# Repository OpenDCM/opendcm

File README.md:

# opendcm
Open DC multimeter.

This repository contain sources for building DC Multimeter.
Project information can be found at :
http://opendcm.blogspot.bg/

The project is still under developing.

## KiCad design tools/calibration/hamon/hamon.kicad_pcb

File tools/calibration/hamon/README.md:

Kicad project for Hamon 1:10 Resistive Divider.

Resistor values can be calculated with the Hamon_calc.ods file.

The first prototype will use :
- S102K 5K resistors for R1-3 
- RCK02 for R4 - 1K8 and R5 - 22K
- Accutrim 1280G 1K trimmer
- 2 SA404 banana plugs for direct connection to the 10V LTZ1000 Voltage Reference Standard
- 2 Pomona 3750 binding posts for cable connection to the DMM
- DPST switch M2021SS1W01 with low contact resistance

Files:<br>
hamon.kicad\_pcb - hamon divider PCB with 2 banana plugs (SA404) and 2 binding posts.<br>
hamon\_bp.kicad\_pcb - hamon divider PCB with 4 binding posts.<br>
Hamon\_calc.ods - spreadsheet for resistor calculation.<br>

Preliminary test:
Setup with Advantest R6581T:

Setup with HP 34401A:

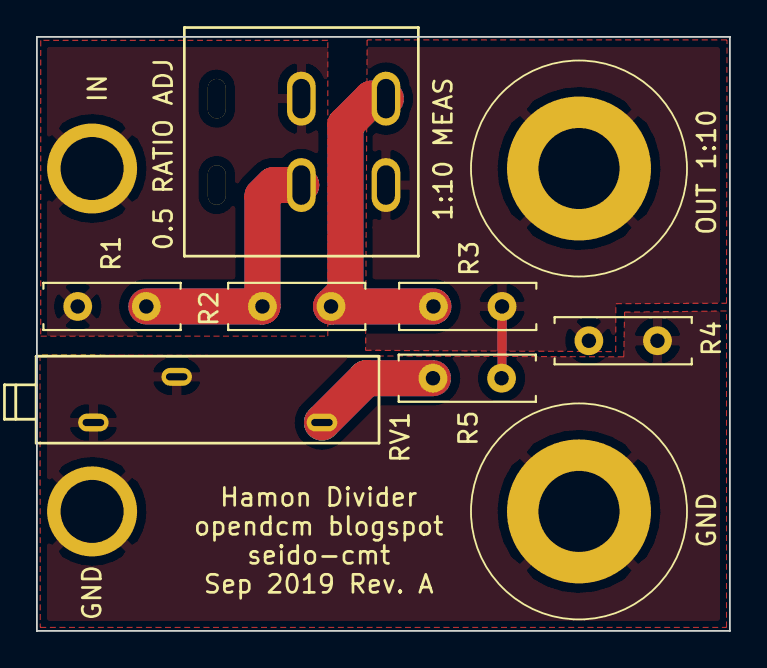
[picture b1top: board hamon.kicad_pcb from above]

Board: 2 copper layers, 38.5 x 33.0 mm, 11 parts (0 on the bottom side), 6 nets.

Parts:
H1: Input; SA404
H2: GND; SA404
H3: Output; Binding_Post_4mm
H4: GND; Binding_Post_4mm
R1, R2, R3, R4, R5: R; Vishay_L7.62mm_D2.67mm_P3.81mm_Horizontal
RV1: R_POT; Accutrim_1280G_1285G
SW1: SW_DPST; M2021SS1W01

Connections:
GND: H2.1, H4.1, R4.2, RV1.2, RV1.3
IN: H1.1, R1.1, SW1.2
unnamed: R1.2, R2.1, SW1.5
unnamed: R2.2, R3.1, SW1.3
unnamed: R5.2, RV1.1
OUT: H3.1, R3.2, R4.1, R5.1, SW1.6

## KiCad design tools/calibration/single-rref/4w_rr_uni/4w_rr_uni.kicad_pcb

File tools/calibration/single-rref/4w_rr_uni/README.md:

This is universal PCB for single resistor reference.
Includes :
- 4 wire connection to the resistor
- Connections with 4 mm banana binding posts and with 4mm banana plugs
- 4 wire connection with pt100 sensor
- I2C EEPROM for storing calibration data

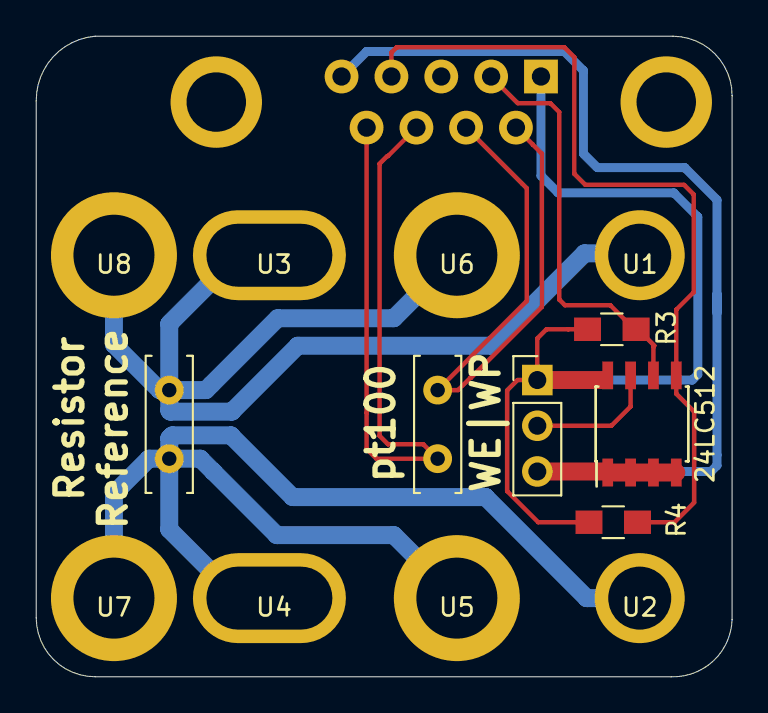
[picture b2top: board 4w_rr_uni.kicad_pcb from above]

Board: 2 copper layers, 38.7 x 35.6 mm, 15 parts (0 on the bottom side), 9 nets.

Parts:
J1: DB9; DB9_horizontal
J2: Conn_01x03; Pin_Header_Straight_1x03_Pitch2.54mm
R1, R2: R; Vishay_L7.62mm_D2.67mm_P3.81mm_Horizontal
R3, R4: R; R_0805_HandSoldering
U1, U2: SA404; VIA
U3, U4: SA404; VIA_oval
U5, U6, U7, U8: Banana; Binding_Post_4mm
U9: 24LC512; SOIC-8_3.9x4.9mm_Pitch1.27mm

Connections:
GND: J1.5, J2.3, U9.1, U9.2, U9.3, U9.4
unnamed: J1.2, R3.2, U9.6
unnamed: J1.4, R4.2, U9.5
unnamed: J1.6, J1.7, R2.1
unnamed: J1.8, J1.9, R2.2
unnamed: J2.2, U9.7
unnamed: R1.1, U1.1, U3.1, U6.1, U8.1
unnamed: R1.2, U2.1, U4.1, U5.1, U7.1
VCC: J1.1, J2.1, R3.1, R4.1, U9.8

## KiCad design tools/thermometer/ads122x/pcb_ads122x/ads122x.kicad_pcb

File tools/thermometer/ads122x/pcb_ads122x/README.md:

This is a PCB for ADS1220, ADS122U04 and ADS122C04 ICs from TI.

The PCB can be used as digital thermometer front-end with PT100 platinum resistance sensor.

The Pt100 sensor can be connected in 2,3,4 wire configuration.

The achievable resolution is 0.001C when 1mA current is used with averaging 20 samples per second.

The achievable uncertainty for 1 year (excluding pt100 probe uncertainty), using a reference resistor with stability <25ppm per year and TCR < 2.5/C can be 0.02C (K=2).

The ADS122x IC have two power supplies - analog AVDD and digital DVDD. This version of PCB have common ground between AVDD and DVDD.

The common ground between AVDD and DVDD limits the temperature range to -20 <-> 145C ( min AVDD = 4V, PGA = 16, Rref = 2.5K).

The PCB can fit into BERNIC ABS box type 40x. 

You can find a spreadsheet document (ADS122x_calculator.ods) which helps to calculate optimal power supplies, PGA pass/fail criteria and RC filters

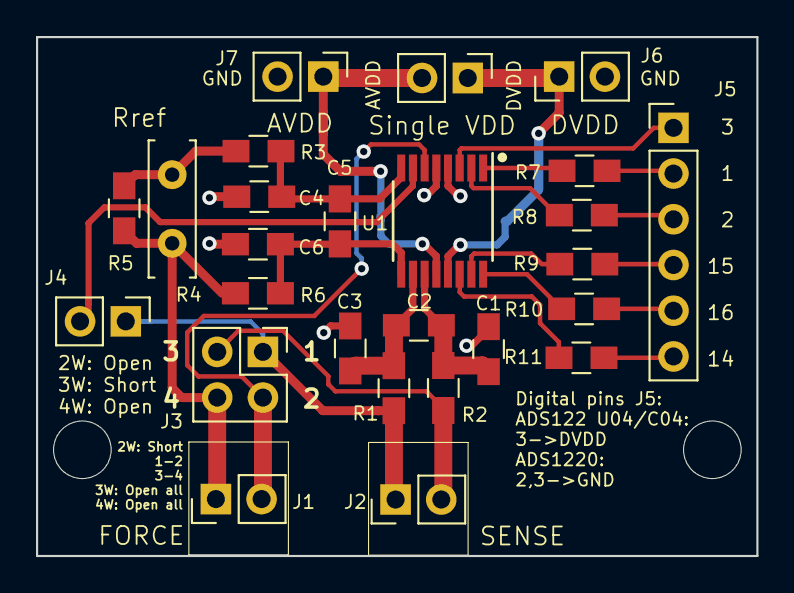
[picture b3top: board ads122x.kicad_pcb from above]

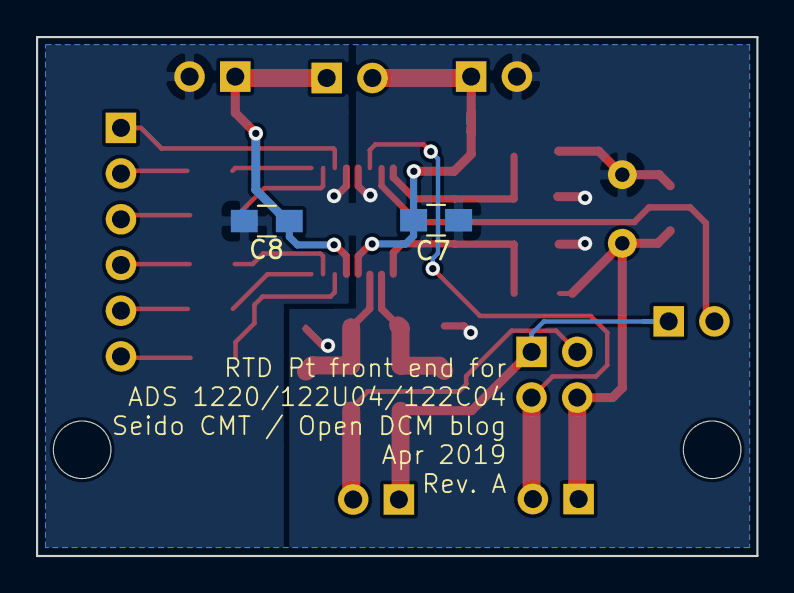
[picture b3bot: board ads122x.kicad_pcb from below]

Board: 2 copper layers, 40.0 x 28.8 mm, 30 parts (2 on the bottom side), 23 nets.

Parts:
C1, C2, C3, C4, C5, C6, C7, C8: C; 0805
H1, H2: MountingHole; MountingHole_3.2mm_M3
J1, J2: Conn_01x02; PCB_Terminal_2_2.54
J3: Conn_02x02_Odd_Even; Pin_Header_Straight_2x02_Pitch2.54mm
J4: Conn_01x02; Pin_Header_Straight_1x02_Pitch2.54mm
J5: Conn_01x06; Pin_Header_Straight_1x06_Pitch2.54mm
J6: Digital Supply; Pin_Header_Straight_1x02_Pitch2.54mm
J7: Analog Supply; Pin_Header_Straight_1x02_Pitch2.54mm
J8: Single Supply; Pin_Header_Straight_1x02_Pitch2.54mm
R1, R2, R3, R5, R6, R7, R8, R9, R10, R11: R; 0805
R4: R; Vishay_L7.62mm_D2.67mm_P3.81mm
U1: ads122x; TSSOP-16_4.4x5mm_Pitch0.65mm

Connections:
AIN0: C1.1, C2.2, R2.2, U1.11
AIN1: C2.1, C3.2, R1.1, U1.10
AIN2: J4.2, U1.7
AIN3: J1.2, J3.2, U1.6
AVDD: C7.2, J7.1, J8.2, U1.12
DVDD: C8.2, J6.1, J8.1, U1.13
GND: C1.2, C3.1, C4.1, C6.1, C7.1, C8.1, J6.2, J7.2, R3.2, R4.2, R5.2, U1.4, U1.5
unnamed: J1.1, J3.4, R4.1, R5.1, R6.2
unnamed: J2.1, J3.1, J4.1, R1.2
unnamed: J2.2, J3.3, R2.1
unnamed: J5.1, U1.3
unnamed: J5.2, R7.1
unnamed: J5.3, R8.1
unnamed: J5.4, R9.1
unnamed: J5.5, R10.1
unnamed: J5.6, R11.1
unnamed: R7.2, U1.1
unnamed: R8.2, U1.2
unnamed: R9.2, U1.15
unnamed: R10.2, U1.16
unnamed: R11.2, U1.14
REFN0: C4.2, C5.2, R3.1, U1.8
REFP0: C5.1, C6.2, R6.1, U1.9

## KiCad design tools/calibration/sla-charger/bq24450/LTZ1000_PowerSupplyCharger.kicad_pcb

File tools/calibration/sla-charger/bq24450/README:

PCB for SLA Battery charger using TI BQ24450 IC.

- Implemention of Fig. 8 and 9a schematics taken from the IC datasheet.
- Darlington transistor.
- Spreadsheet for resisors calculation and power dissipation estimation.
- Under Voltage Detection (UVD).
- Input polarity protection.
- LDO output.
- Power On / Charging / UVD LEDs.

ChangeLog:

Rev. D (24 May 2019)
- Added polarity protection.
- Added schematics for custom I tapper value (not the defualt one 10% from charging current).
   This will allow the PCB to be used in the cases when a load is permanently connected to the battery.
- Updated the calculation document.
- Removed the capacitor from the rev. C.
- Increased tracks width.
This version of the PCB is not yet produced and tested.

Rev. C (14 April 2019)
- Fixed issue when the power is switched on and the battery is in floating mode only.
  The issue was resolved with adding 1uF capacitor accross the Rdx resistors.
- Changed Under Voltage Detector resistors divider values to fullfill >100uA requirement from the TC54 datasheet 
This version of the PCB is not yet produced and tested.

Rev. B (22 March 2018)
- Fixed missing connection between Vin and LED supply rail
- Decreased sense resistors to 3 only.
- Decreased PCB size.
- Added double resistors for coarse/fine addjustments.

Rev. A (21 December 2018)
Prototype initial revision with 7 sense resistors. This version was not stored into the github.

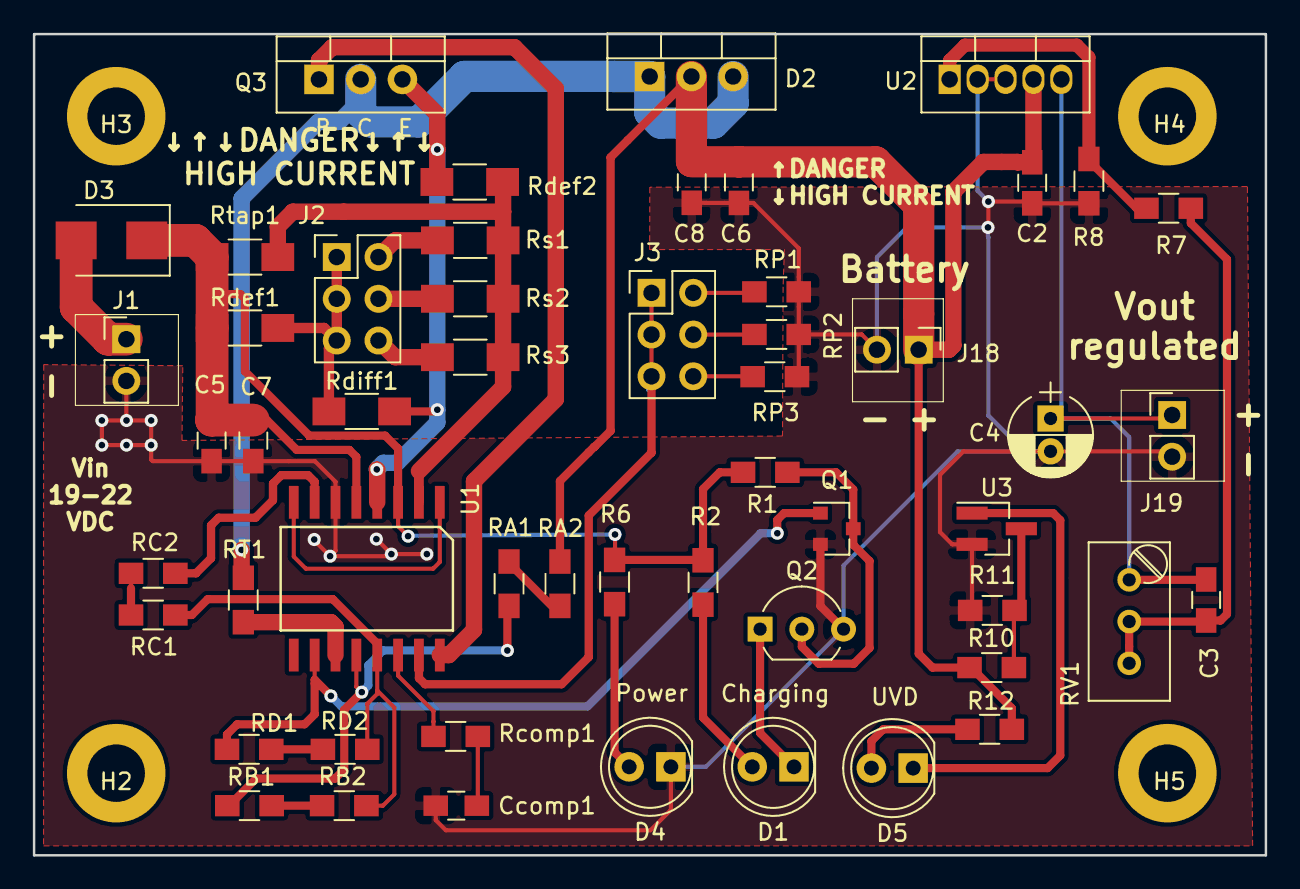
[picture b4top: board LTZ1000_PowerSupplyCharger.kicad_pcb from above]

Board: 2 copper layers, 75.0 x 50.0 mm, 57 parts (0 on the bottom side), 38 nets.

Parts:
C2: 0.22uF; C_0805_HandSoldering
C3: 1nF; C_0805_HandSoldering
C4: 22uF; CP_Radial_D5.0mm_P2.00mm
C5, C8: 1uF; C_0805_HandSoldering
C6, C7: 0.1uF; C_0805_HandSoldering
Ccomp1: 0.22uF; C_0805_HandSoldering
D1: Charging; LED_D5.0mm
D2: SR1640; TO-220-3_Vertical
D3: D; D_SMB
D4: Power; LED_D5.0mm
D5: UVD; LED_D5.0mm
H2, H3, H4, H5: MountingHole; NPTH
J1: Vin; PCB_Terminal_2_2.54
J2: Charging; Pin_Header_Straight_2x03_Pitch2.54mm
J3: PowerDispersion; Pin_Header_Straight_2x03_Pitch2.54mm
J18: Battery; PCB_Terminal_2_2.54
J19: Vout; PCB_Terminal_2_2.54
Q1: BSS138; SOT-23
Q2: BC547; TO-92_Inline_Wide
Q3: B C E; TO-220-3_Vertical
R1: 330k; R_0805_HandSoldering
R2, R6: 6k8; R_0805_HandSoldering
R7: 750k; R_0805_HandSoldering
R8: 102k; R_0805_HandSoldering
R10: 45.3K; R_0805_HandSoldering
R11: 28K; R_0805_HandSoldering
R12: 6K8; R_0805_HandSoldering
RA1: 200K; R_0805_HandSoldering
RA2: 10K; R_0805_HandSoldering
RB1: 0; R_0805_HandSoldering
RB2: 12K; R_0805_HandSoldering
RC1: 45.3K; R_0805_HandSoldering
RC2: 0; R_0805_HandSoldering
RD1: 430K; R_0805_HandSoldering
RD2: 20K; R_0805_HandSoldering
RP1: 43K; R_0805_HandSoldering
RP2: 22K1; R_0805_HandSoldering
RP3: 15K; R_0805_HandSoldering
RT1: 510; R_0805_HandSoldering
RV1: 200K; Potentiometer_Trimmer_Bourns_3296W
Rcomp1: 470; R_0805_HandSoldering
Rdef1, Rdef2: 0R; R_1206_HandSoldering
Rdiff1: 0R; R_1206_HandSoldering
Rs1, Rs2, Rs3: 0R68; R_1206_HandSoldering
Rtap1: 0R; R_1206_HandSoldering
U1: BQ24450; SOIC-16
U2: MIC2940; TO-220-5_Vertical
U3: TC54; SOT-23_Handsoldering

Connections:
GND: C2.2, C4.2, C5.2, C6.2, C7.2, C8.2, Ccomp1.2, D4.1, J1.2, J18.2, J19.2, Q1.2, Q2.3, R8.1, R11.1, RP1.2, RP2.2, RP3.2, U1.6, U2.2, U2.3, U3.2
unnamed: C3.1, C4.1, J19.1, RV1.1, U2.5
unnamed: C3.2, R7.2, RV1.2, RV1.3
unnamed: Ccomp1.1, Rcomp1.1
unnamed: D1.1, Q2.1
unnamed: D1.2, R2.1
unnamed: D2.1, D2.3, Q3.2, RT1.2
unnamed: D3.2, J1.1
unnamed: D4.2, R6.1
unnamed: D5.1, U3.1
unnamed: D5.2, R12.1
unnamed: J2.1, J2.3, J2.5, Rdef1.2, Rdiff1.1
unnamed: J2.2, Rs1.2
unnamed: J2.4, Rs2.2
unnamed: J2.6, Rs3.2
unnamed: J3.1, J3.3, J3.5, U1.15
unnamed: J3.2, RP1.1
unnamed: J3.4, RP2.1
unnamed: J3.6, RP3.1
unnamed: Q1.3, Q2.2, R1.1
unnamed: Q3.1, U1.16
unnamed: Q3.3, Rdef2.2, Rdiff1.2, U1.4
unnamed: R7.1, R8.2, U2.1
unnamed: R10.1, R11.2, U3.3
unnamed: RA1.1, RB1.1, U1.12
unnamed: RA1.2, RA2.1
unnamed: RB1.2, RB2.2
unnamed: RB2.1, RC1.2, RD2.2, U1.13
unnamed: RC1.1, RC2.2
unnamed: RC2.1, U1.7
unnamed: RD1.2, RD2.1
unnamed: RT1.1, U1.11
unnamed: Rcomp1.2, U1.14
unnamed: Rdef2.1, Rs1.1, Rs2.1, Rs3.1, Rtap1.1, U1.2
unnamed: U1.1, U1.8
STAT1: Q1.1, RD1.1, U1.10
VBatt: C2.1, C6.1, C8.1, D2.2, J18.1, R10.2, R12.2, RA2.2, U2.4
Vin: C5.1, C7.1, D3.1, R1.2, R2.2, R6.2, Rdef1.1, Rtap1.2, U1.3, U1.5

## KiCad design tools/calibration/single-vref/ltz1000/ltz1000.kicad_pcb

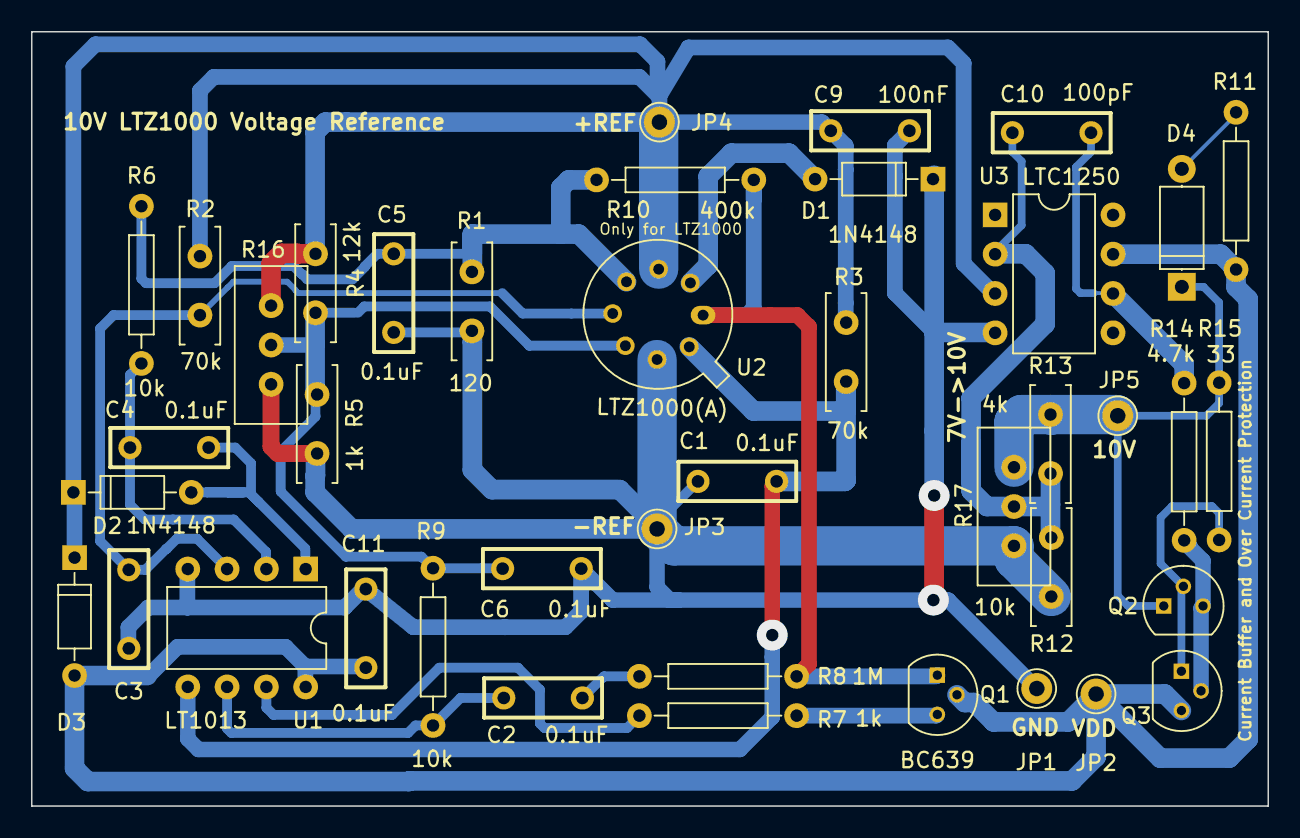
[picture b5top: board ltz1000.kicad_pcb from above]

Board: 2 copper layers, 79.9 x 50.0 mm, 41 parts (0 on the bottom side), 21 nets.

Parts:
C1, C2, C4, C5, C6, C11: 0.1uF; C
C3: 22nF; C
C9: 100nF; C
C10: 100pF; C
D1, D2, D3: 1N4148; D_DO-35_SOD27_P7.62mm_Horizontal
D4: LED; D_A-405_P7.62mm_Horizontal
JP1, JP2, JP3, JP4, JP5: CONN_1X1; Pin_d1.0mm_L10.0mm
Q1: BC639; TO-92_Molded_Narrow
Q2, Q3: NPN_CBE; TO-92_Molded_Narrow
R1: 120; Vishay_L7.62mm_D2.67mm_P3.81mm_Horizontal
R2, R3: 70k; Vishay_L7.62mm_D2.67mm_P3.81mm_Horizontal
R4: 12k; Vishay_L7.62mm_D2.67mm_P3.81mm_Horizontal
R5: 1k; Vishay_L7.62mm_D2.67mm_P3.81mm_Horizontal
R6, R9: 10k; R_Axial_L6.3mm_D2.0mm_P10.16mm_Horizontal
R7: 1k; R_Axial_L6.3mm_D2.0mm_P10.16mm_Horizontal
R8: 1M; R_Axial_L6.3mm_D2.0mm_P10.16mm_Horizontal
R10: 400k; R_Axial_L6.3mm_D2.0mm_P10.16mm_Horizontal
R11: 2K; R_Axial_L6.3mm_D2.0mm_P10.16mm_Horizontal
R12: 10k; Vishay_L7.62mm_D2.67mm_P3.81mm_Horizontal
R13: 4k; Vishay_L7.62mm_D2.67mm_P3.81mm_Horizontal
R14: 4.7k; R_Axial_L6.3mm_D2.0mm_P10.16mm_Horizontal
R15: 33; R_Axial_L6.3mm_D2.0mm_P10.16mm_Horizontal
R16, R17: R_FOIL_DIVIDER; Vishay_VHD_L10.11mm_D4.7mm_P2.54mm_Horizontal
U1: LT1013; DIP-8_W7.62mm
U2: LTZ1000(A); TO-5-8
U3: LTC1250; DIP-8_W7.62mm

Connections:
10.00000V: D4.1, JP5.1, Q2.1, R13.1, R15.1, R17.1
+REF: C9.1, D2.1, D3.1, JP4.1, R2.1, R3.1, R4.1, R16.1, U2.3, U3.3
-REF: C1.2, C3.2, C5.2, C6.2, C9.2, C11.2, D1.1, JP1.1, JP3.1, R1.2, R5.2, R12.2, R16.3, R17.3, U1.4, U2.7, U3.4
H+: Q1.1, R8.1, R10.2, U2.1
unnamed: C1.1, R3.2, U1.5, U2.8
unnamed: C2.1, R9.2, U1.6
unnamed: C2.2, R8.2
unnamed: C3.1, R2.2, U1.3, U2.5
unnamed: C4.1, R6.1, U1.2
unnamed: C4.2, D2.2, U1.1
unnamed: C5.1, R1.1, R6.2, R10.1, U2.4
unnamed: C6.1, R4.2, R5.1, R9.1, R16.2, U2.6
unnamed: C10.1, R12.1, R13.2, R17.2, U3.2
unnamed: C10.2, R14.2, U3.6
unnamed: D1.2, U2.2
unnamed: D4.2, R11.1
unnamed: Q1.3, R7.2
unnamed: Q2.2, Q3.1, R15.2
unnamed: Q2.3, Q3.2, R14.1
unnamed: R7.1, U1.7
VDD: C11.1, D3.2, JP2.1, Q1.2, Q3.3, R11.2, U1.8, U3.7

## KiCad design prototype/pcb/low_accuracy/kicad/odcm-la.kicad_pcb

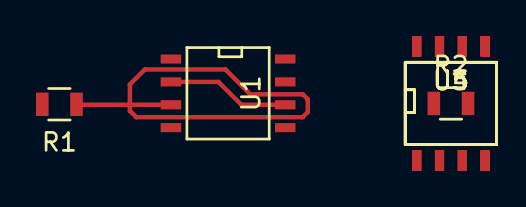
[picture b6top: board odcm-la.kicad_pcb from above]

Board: 2 copper layers, 6 parts (0 on the bottom side), 5 nets.

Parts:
R1, R2: 1K; R_0805
U1, U3, U4, U5: LTC2057; SOIC-8-N

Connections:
unnamed: R1.1, U1.3
unnamed: R2.1, U3.3
unnamed: R2.2, U1.2, U1.6
unnamed: U3.2, U3.6
unnamed: U5.2, U5.6

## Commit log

2016-03-06 Test commit
2016-03-06 Added link to opendcm.blogspot.bg
2016-04-04 Initial commit for breadboard prototype. Includes kicad project and arduino firmware for pro micro board.
2016-04-04 Minor README formatting
2016-04-06 Added ohmmeter
2016-04-06 Deleted backup kicad library files
2016-04-06 Deleted the empty kicad pcb file for the ohmmeter
2016-04-12 Added negative voltage measurement. Fixed switching between detail and not-detail mode
2016-06-11 Added LTSpice sim for Auto Voltage Range and Over Voltage Protection using Schottky diodes
2016-06-11 Added the second schottky diode
2016-06-11 Added simulation for handling input negative voltage
2016-06-13 Added all in one simulation and bipolar auto voltage range
2016-06-13 Change input voltage from 13.75 to 12 due voltage supply limitation
2016-08-28 Added dual supply schematics for ADC LTC2440
2016-09-02 Added automatic voltage range
2016-09-02 Added new components and hierarchy sheets
2016-09-02 Fixed LT5400wrong connection in Auto Voltage Range schematics
2016-09-06 More buffers are added for resolving found issues.
2016-09-16 fixed voltage of the opamp
2016-09-18 Repaced with LTC2057 the opamp directly connected after the input buffer. It should handle input voltage.
2016-10-23 Added initial PCB prototype kicad files. Only chematics is done.
2019-03-23 Added LTZ1000, SLA charger and zero calibration tools
2019-04-14 Rev. C - Fixed issue when the power is switched on and the battery stayed in floating mode. The issue was resolved with adding 1uF capacitor accross the Rdx resistors. - Changed Under Voltage Detecto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
2019-04-14 Added README file
2019-05-24 1. Updated the calculation document. 2. Added schematics for custom I tapper value (not the defualt one 10% from charging current). This will allow the PCB to be used in the cases when a load is conn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
2019-05-24 Updated README file
2019-08-07 Added initial version of PCB for ADS122x based digital thermometer
    This PCB supports ADS1220, ADS122U04 and ADS122C04 ICs from TI.
2019-08-07 Modifying README to include rendered 3D view of the PCB
2019-08-07 Trying to add image into README.md
2019-08-07 Added real PCB picture.
2019-08-15 Added ADS122x calculator.
2019-08-21 Added values for caps and resistors in ADS122x schematics.
2019-09-05 Added single resistor reference PCB.
2019-09-07 Initial commit for Hamon divider.
2019-09-07 Added remark in the README.md that Hamon divider is not yet ready and tested.
2019-09-07 Better README.md layout.
2019-09-08 Added second hamon divider PCB with binding posts only. The first variant was with SA404 4mm banana plugs for direct plugin into the voltage reference.
2019-09-08 Updated README.md for hamon pcb version with 4 binding posts.
2020-07-15 Added updated hamon divider PCB
2020-07-15 Fixed issue with symbol library. Added pdf schematics. Updated and clean up schematics.
2020-07-15 Update README for Hamon divider
    Added images of the hamon divder
2020-07-15 Update README.md
    Added hamon divider images in README
2020-07-15 Update README.md
    Updated links for images
2020-07-15 Added reduced images for hamon divider
2020-07-16 Added schemtics for the ads122x based thermometer.
